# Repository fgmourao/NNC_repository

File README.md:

# NNC_repository
Custom equipments for open source science. Developed  by the Núcleo de Neurociências (Neuroscience Research Center) at the Federal University of Minas Gerais (Brazil).

Núcleo de Neurociências (Neuroscience Research Center)<br />
Department of Physiology and Biophysics<br />
Institute of Biological Sciences (ICB) <br />
Federal University of Minas Gerais  (UFMG)<br />
Av. Antônio Carlos, 6627 - Postal Code:  31270-901 - Campus Pampulha<br />
Belo Horizonte - MG - Brazil<br />
Phone: +55 31 3409-2930

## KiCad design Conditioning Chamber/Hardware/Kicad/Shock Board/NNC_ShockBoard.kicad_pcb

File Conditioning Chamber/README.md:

# A Custom Microcontrolled and Wireless-Operated Chamber for Auditory Fear Conditioning

Authors: Paulo Aparecido Amaral Júnior1,2#, Flávio Afonso Gonçalves Mourão1#, Mariana Chamon Ladeira Amâncio1, Hyorrana Pereira Pinto1, Vinícius Rezende Carvalho1,2, Leonardo de Oliveira Guarnieri1,2, Hermes Aguiar Magalhães2, Márcio Flávio Dutra Moraes1*. 

1 - Núcleo de Neurociências, Departamento de Fisiologia e Biofísica, Instituto de Ciências Biológicas (ICB), Universidade Federal de Minas Gerais (UFMG). Av. Antônio Carlos, 6627 - CEP 31270-901. Belo Horizonte, Minas Gerais, Brazil.<br />
2 - Programa de Pós-Graduação em Engenharia Elétrica, Departamento de Engenharia Eletrônica (DELT), Escola de Engenharia, Universidade Federal de Minas Gerais (UFMG). Av. Antônio Carlos, 6627 - CEP 31270-901. Belo Horizonte, Minas Gerais, Brazil.<br />

Animal behavioral paradigms, such as classical conditioning and operant conditioning, are an important tool to study the neural basis of cognition and behavior. These paradigms involve manipulating sensory stimuli in a way that learning processes are induced under controlled experimental conditions. However, the majority of the commercially available equipment did not offer flexibility to manipulate stimuli. Therefore, the development of most versatile devices would allow the study of more complex cognitive functions. The purpose of this work is to present a low-cost, customized and wireless-operated chamber for animal behavior conditioning, based on the joint operation of two microcontroller modules: Arduino Due and ESP8266-12E. Our results showed that the auditory stimulation system allows setting the carrier frequency in the range of 1 Hz up to more than 100 kHz and the sound stimulus can be modulated in amplitude, also over a wide range of frequencies. Likewise, foot-shock could be precisely manipulated regarding its amplitude (from ~200 μA to ~1500 μA) and frequency (up to 20 pulses per second). Finally, adult rats exposed to a protocol of cued fear conditioning in our device showed consistent behavioral response and electrophysiological evoked responses in the midbrain auditory pathway. Furthermore, the device developed in the current study represents an open source alternative to develop customized protocols to study fear memory under conditions of varied sensory stimuli. 

Paper published in Frontiers in Neuroscience | www.frontiersin.org
https://www.frontiersin.org/articles/10.3389/fnins.2019.01193/full

Correspondence:<br />

Flávio Afonso Gonçalves Mourão, PhD<br />
Núcleo de Neurociências, Departamento de Fisiologia e Biofísica<br />
Instituto de Ciências Biológicas (ICB)<br /> 
Universidade Federal de Minas Gerais (UFMG)<br />
Av. Antônio Carlos, 6627 - CEP 31270-901- Campus Pampulha<br />
Belo Horizonte - MG - Brazil<br />
Fax: +55 31 3409-2924 Phone: +55 31 3409-2927<br />
Email: mourao.fg@gmail.com<br />

Márcio Flávio Dutra Moraes, PhD<br />
Núcleo de Neurociências, Departamento de Fisiologia e Biofísica<br />
Instituto de Ciências Biológicas (ICB)<br /> 
Universidade Federal de Minas Gerais (UFMG)<br />
Av. Antônio Carlos, 6627 - CEP 31270-901- Campus Pampulha<br />
Belo Horizonte - MG - Brazil<br />
Fax: +55 31 3409-2924 Phone: +55 31 3409-2930<br />
Email: mfdm@icb.ufmg.br<br />

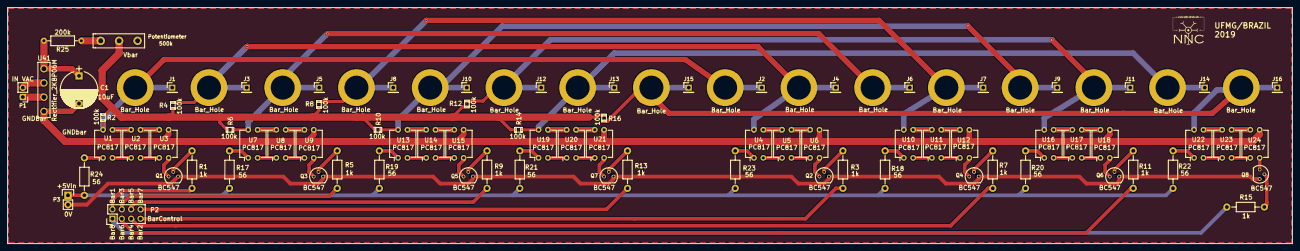
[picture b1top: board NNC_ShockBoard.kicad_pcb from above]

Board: 2 copper layers, 348.5 x 64.0 mm, 95 parts (0 on the bottom side), 80 nets.

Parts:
C1: 10uF; CP_Radial_D10.0mm_P7.50mm
J1, J2, J3, J4, J5, J6, J7, J8, J9, J10, J11, J12, J13, J14, J15, J16: Conn_01x01; Pin_Header_Straight_1x01_Pitch2.54mm
P1: IN VAC; Pin_Header_Straight_1x02_Pitch2.54mm
P2: CONN_01X08; Pin_Header_Straight_2x04
P3: 5VDC In; Pin_Header_Straight_1x02
Potentiometer: 500k; Potentiometer_Alps_RK163_Single_Vertical
Q1, Q2, Q3, Q4, Q5, Q6, Q7, Q8: BC547; TO-92_Molded_Narrow
R1, R3, R5, R7, R9, R11, R13, R15: 1k; Resistor_Horizontal_RM10mm
R2, R4, R6, R8, R10, R12, R14, R16: 100k; SMD_0805
R17, R18, R19, R20, R21, R22, R23, R24: 56; Resistor_Horizontal_RM10mm
R25: 200k; R_Axial_DIN0207_L6.3mm_D2.5mm_P10.16mm_Horizontal
U1, U2, U3, U4, U5, U6, U7, U8, U9, U10, U11, U12, U13, U14, U15, U16, U17, U18, U19, U20, U21, U22, U23, U24: PC817; DIP-4_W7.62mm
U25, U26, U27, U28, U29, U30, U31, U32, U33, U34, U35, U36, U37, U38, U39, U40: Bar_Hole
U41: Rectifier_2KBP06M

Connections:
5V_Arduino: P3.1, R17.2, R18.2, R19.2, R20.2, R21.2, R22.2, R23.2, R24.2
/InBarra1: P2.2, R1.2
/InBarra2: P2.7, R3.2
/InBarra3: P2.4, R5.2
/InBarra4: P2.5, R7.2
/InBarra5: P2.6, R9.2
/InBarra6: P2.3, R11.2
/InBarra7: P2.8, R13.2
/InBarra8: P2.1, R15.2
/OutBarra1: J1.1, J2.1, R2.2, U1.4, U25.1, U33.1
/OutBarra2: J3.1, J4.1, R4.2, U4.4, U26.1, U34.1
/OutBarra3: J5.1, J6.1, R6.2, U7.4, U27.1, U35.1
/OutBarra4: J7.1, J8.1, R8.2, U10.4, U28.1, U36.1
/OutBarra5: J9.1, J10.1, R10.2, U13.4, U29.1, U37.1
/OutBarra6: J11.1, J12.1, R12.2, U16.4, U30.1, U38.1
/OutBarra7: J13.1, J14.1, R14.2, U19.4, U31.1, U39.1
/OutBarra8: J15.1, J16.1, R16.2, U22.4, U32.1, U40.1
/Vtrafo+: P1.1, U41.3
/Vtrafo-: P1.2, U41.2
GndArduino: P3.2, Q1.3, Q2.3, Q3.3, Q4.3, Q5.3, Q6.3, Q7.3, Q8.3
GndBarra: C1.2, U3.3, U6.3, U9.3, U12.3, U15.3, U18.3, U21.3, U24.3, U41.4
unnamed: C1.1, R25.2, U41.1
unnamed: Q1.1, U3.2
unnamed: Q1.2, R1.1
unnamed: Q2.1, U6.2
unnamed: Q2.2, R3.1
unnamed: Q3.1, U9.2
unnamed: Q3.2, R5.1
unnamed: Q4.1, U12.2
unnamed: Q4.2, R7.1
unnamed: Q5.1, U15.2
unnamed: Q5.2, R9.1
unnamed: Q6.1, U18.2
unnamed: Q6.2, R11.1
unnamed: Q7.1, U21.2
unnamed: Q7.2, R13.1
unnamed: Q8.1, U24.2
unnamed: Q8.2, R15.1
unnamed: R17.1, U7.1
unnamed: R18.1, U10.1
unnamed: R19.1, U13.1
unnamed: R20.1, U16.1
unnamed: R21.1, U19.1
unnamed: R22.1, U22.1
unnamed: R23.1, U4.1
unnamed: R24.1, U1.1
unnamed: Potentiometer.3, R25.1
unnamed: U1.2, U2.1
unnamed: U1.3, U2.4
unnamed: U2.2, U3.1
unnamed: U2.3, U3.4
unnamed: U4.2, U5.1
unnamed: U4.3, U5.4
unnamed: U5.2, U6.1
unnamed: U5.3, U6.4
unnamed: U7.2, U8.1
unnamed: U7.3, U8.4
unnamed: U8.2, U9.1
unnamed: U8.3, U9.4
unnamed: U10.2, U11.1
unnamed: U10.3, U11.4
unnamed: U11.2, U12.1
unnamed: U11.3, U12.4
unnamed: U13.2, U14.1
unnamed: U13.3, U14.4
unnamed: U14.2, U15.1
unnamed: U14.3, U15.4
unnamed: U16.2, U17.1
unnamed: U16.3, U17.4
unnamed: U17.2, U18.1
unnamed: U17.3, U18.4
unnamed: U19.2, U20.1
unnamed: U19.3, U20.4
unnamed: U20.2, U21.1
unnamed: U20.3, U21.4
unnamed: U22.2, U23.1
unnamed: U22.3, U23.4
unnamed: U23.2, U24.1
unnamed: U23.3, U24.4
Vbarra: Potentiometer.2, R2.1, R4.1, R6.1, R8.1, R10.1, R12.1, R14.1, R16.1

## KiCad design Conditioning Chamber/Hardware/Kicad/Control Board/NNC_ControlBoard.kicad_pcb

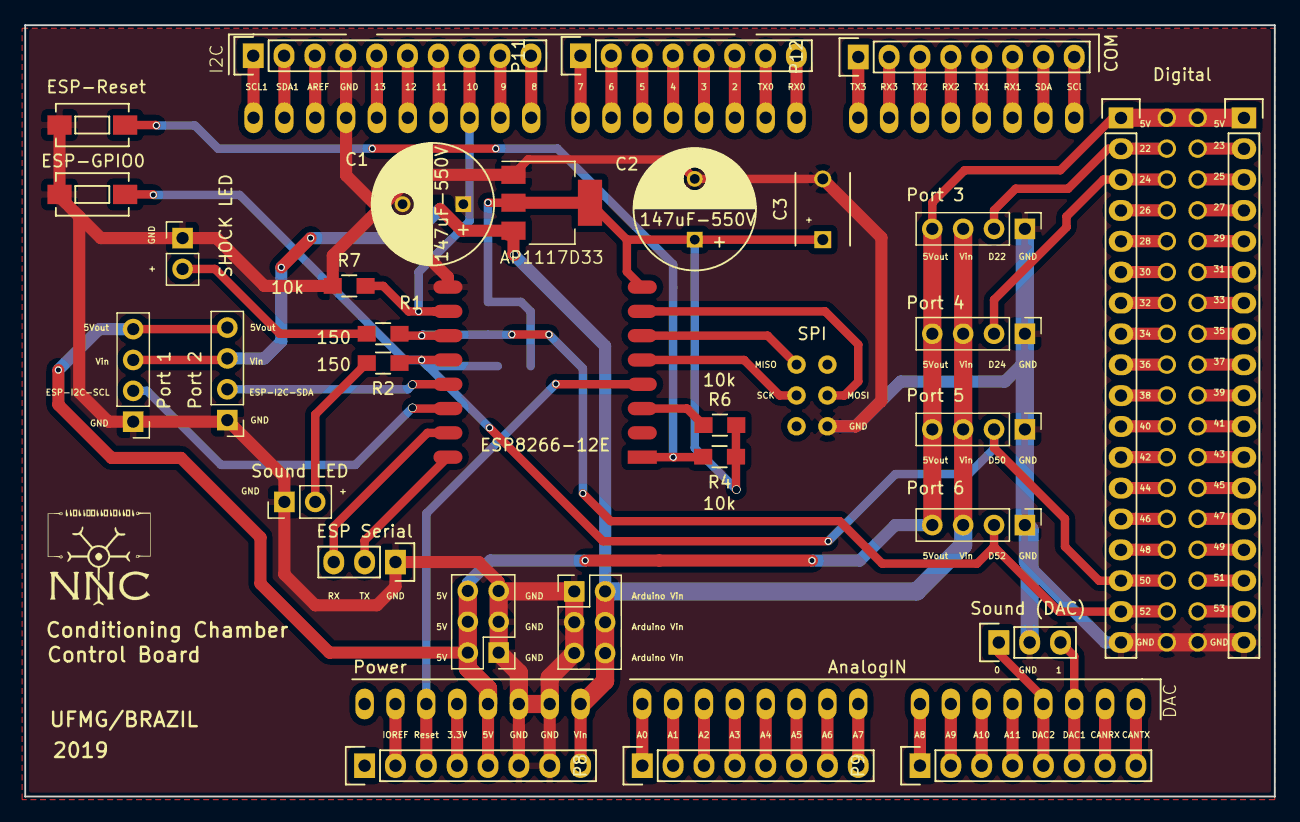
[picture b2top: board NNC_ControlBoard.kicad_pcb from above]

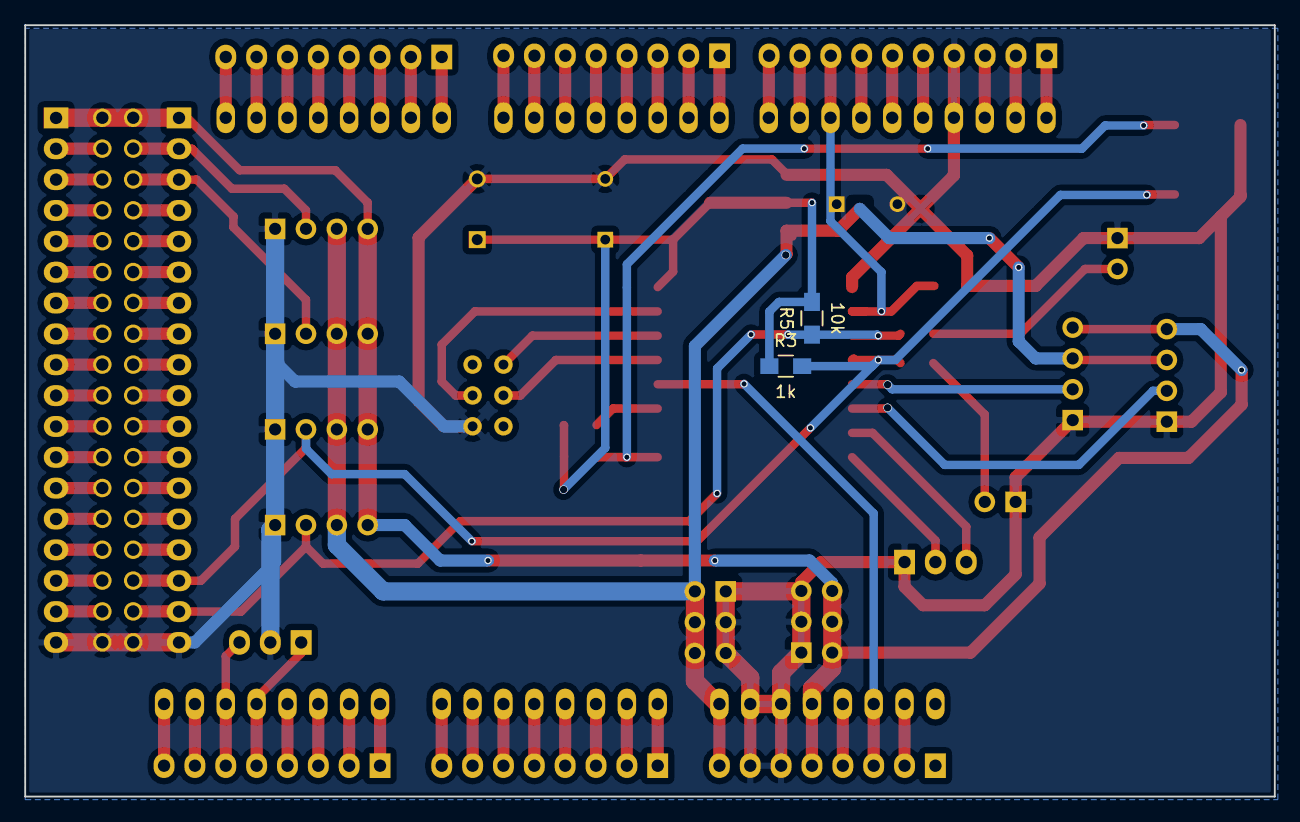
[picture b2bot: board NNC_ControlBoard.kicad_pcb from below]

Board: 2 copper layers, 102.9 x 63.5 mm, 35 parts (2 on the bottom side), 91 nets.

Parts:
C1, C2: 147uF-550V; C_Radial_D10_L13_P5
C3: C; C_Disc_D6_P5
Control Board: Conditioning Chamber; ARDUINO_DUE_SHIELD
D1: SHOCK LED; Pin_Header_Straight_1x02_Pitch2.54mm
D2: Sound LED; Pin_Header_Straight_1x02_Pitch2.54mm
ESP1: ESP8266-12E; ESP-12E_noBottomPads
ESP-GPIO0: 2; SW_SPST_EVQPE1
ESP-Reset: 1; SW_SPST_EVQPE1
I2C: PWM2; Pin_Header_Straight_1x10
J1: Port 6; Pin_Header_Straight_1x04_Pitch2.54mm
J2: Port 2; Pin_Header_Straight_1x04_Pitch2.54mm
J3: Port 3; Pin_Header_Straight_1x04_Pitch2.54mm
J4: Port 4; Pin_Header_Straight_1x04_Pitch2.54mm
J5: Port 5; Pin_Header_Straight_1x04_Pitch2.54mm
J6: Port 1; Pin_Header_Straight_1x04_Pitch2.54mm
J7: Arduino Vin; Pin_Header_Straight_2x03_Pitch2.54mm
J8: 5V; Pin_Header_Straight_2x03_Pitch2.54mm
P3: Sound (DAC); Pin_Header_Straight_1x03
P4: ESP Serial; Pin_Header_Straight_1x03
P5: DIG1; Pin_Header_Straight_1x18
P6: DIG2; Pin_Header_Straight_1x18
P7: Power; Pin_Header_Straight_1x08
P8: AnalogIN; Pin_Header_Straight_1x08
P9: DAC; Pin_Header_Straight_1x08
P11: PWM1; Pin_Header_Straight_1x08
P12: COM; Pin_Header_Straight_1x08
R1, R2: 150; R_0805_HandSoldering
R3: 1k; R_0805_HandSoldering
R4, R5, R6, R7: 10k; R_0805_HandSoldering
U1: AP1117D33; SOT-223-3_TabPin2

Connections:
/5Voutput: Control Board.5V, Control Board.5V_4, Control Board.5V_5, J1.4, J2.4, J3.4, J4.4, J5.4, J6.4, J8.2, J8.4, J8.6, P5.1, P6.1, P7.5
/Arduino_Vin: C1.1, Control Board.V_IN, J1.3, J2.3, J3.3, J4.3, J5.3, J6.3, J7.2, J7.4, J7.6, P7.8, U1.3
/D22: Control Board.22, J3.2, P5.2
/D23: Control Board.23, P6.2
/D24: Control Board.24, J4.2, P5.3
/D25: Control Board.25, P6.3
/D26: Control Board.26, P5.4
/D27: Control Board.27, P6.4
/D28: Control Board.28, P5.5
/D29: Control Board.29, P6.5
/D30: Control Board.30, P5.6
/D31: Control Board.31, P6.6
/D32: Control Board.32, P5.7
/D33: Control Board.33, P6.7
/D34: Control Board.34, P5.8
/D35: Control Board.35, P6.8
/D36: Control Board.36, P5.9
/D37: Control Board.37, P6.9
/D38: Control Board.38, P5.10
/D39: Control Board.39, P6.10
/D40: Control Board.40, P5.11
/D41: Control Board.41, P6.11
/D42: Control Board.42, P5.12
/D43: Control Board.43, P6.12
/D44: Control Board.44, P5.13
/D45: Control Board.45, P6.13
/D46: Control Board.46, P5.14
/D47: Control Board.47, P6.14
/D48: Control Board.48, P5.15
/D49: Control Board.49, P6.15
/D50: Control Board.50, ESP1.18, ESP-GPIO0.1, J5.2, P5.16, R2.1, R3.2
/D51: Control Board.51, P6.16
/D52: Control Board.52, ESP1.17, J1.2, P5.17, R1.1, R5.1
/D53: Control Board.53, P6.17
/DAC0: Control Board.DAC0, P3.1, P9.5
/DAC1: Control Board.DAC1, P3.3, P9.6
/ESP12Econfig/ESPchpd: ESP1.3, R6.1
/ESP12Econfig/ESPrst: ESP1.1, ESP-Reset.1, R4.2
/ESP12Econfig/VDD3V: C2.1, C3.1, ESP1.8, R3.1, R4.1, R5.2, R6.2, U1.2
/ESP_CS: Control Board.10, ESP1.16, I2C.8, R7.2
/ESP_GPIO16: Control Board.RST, ESP1.4, P7.3
/ESP_I2C_SCL: ESP1.20, J6.2
/ESP_I2C_SDA: ESP1.19, J2.2
/ESP_MISO: Control Board.SP1, ESP1.6
/ESP_MOSI: Control Board.SP4, ESP1.7
/ESP_RX: ESP1.21, P4.3
/ESP_SCK: Control Board.SP3, ESP1.5
/ESP_TX: ESP1.22, P4.2
/GND: C1.2, C2.2, C3.2, Control Board.GND1, Control Board.GND2, Control Board.GND3, Control Board.GND4, Control Board.GND5, Control Board.SP6, D1.1, D2.1, ESP1.15, ESP-GPIO0.2, ESP-Reset.2, I2C.4, J1.1, J2.1, J3.1, J4.1, J5.1, J6.1, J7.1, J7.3, J7.5, J8.1, J8.3, J8.5, P3.2, P4.1, P5.18, P6.18, P7.6, P7.7, R7.1, U1.1
unnamed: D1.2, R1.2
unnamed: D2.2, R2.2
unnamed: Control Board.IO_R, P7.2
unnamed: Control Board.3V3, P7.4
unnamed: Control Board.AD0, P8.1
unnamed: Control Board.AD1, P8.2
unnamed: Control Board.AD2, P8.3
unnamed: Control Board.AD3, P8.4
unnamed: Control Board.AD4, P8.5
unnamed: Control Board.AD5, P8.6
unnamed: Control Board.AD6, P8.7
unnamed: Control Board.AD7, P8.8
unnamed: Control Board.AD8, P9.1
unnamed: Control Board.AD9, P9.2
unnamed: Control Board.AD10, P9.3
unnamed: Control Board.AD11, P9.4
unnamed: Control Board.C_RX, P9.7
unnamed: Control Board.C_TX, P9.8
unnamed: Control Board.SCL1, I2C.1
unnamed: Control Board.SDA1, I2C.2
unnamed: Control Board.AREF, I2C.3
unnamed: Control Board.13, I2C.5
unnamed: Control Board.12, I2C.6
unnamed: Control Board.11, I2C.7
unnamed: Control Board.9, I2C.9
unnamed: Control Board.8, I2C.10
unnamed: Control Board.7, P11.1
unnamed: Control Board.6, P11.2
unnamed: Control Board.5, P11.3
unnamed: Control Board.4, P11.4
unnamed: Control Board.3, P11.5
unnamed: Control Board.2, P11.6
unnamed: Control Board.1, P11.7
unnamed: Control Board.0, P11.8
unnamed: Control Board.14, P12.1
unnamed: Control Board.15, P12.2
unnamed: Control Board.16, P12.3
unnamed: Control Board.17, P12.4
unnamed: Control Board.18, P12.5
unnamed: Control Board.19, P12.6
unnamed: Control Board.20, P12.7
unnamed: Control Board.21, P12.8

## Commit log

2019-08-16 Update 16-08-19
2019-11-07 update 07-11-19
2019-11-19 update19-11-19
2019-11-19 Update 19-11-19
    - Control box New Version (2.0). New box Design and Audio Amplifier (LM386) add to the project.
    - Article published in Frontiers in Neuroscience | www.frontiersin.org
2019-11-19 Update 19-11-19
2019-12-01 Update nov-19
